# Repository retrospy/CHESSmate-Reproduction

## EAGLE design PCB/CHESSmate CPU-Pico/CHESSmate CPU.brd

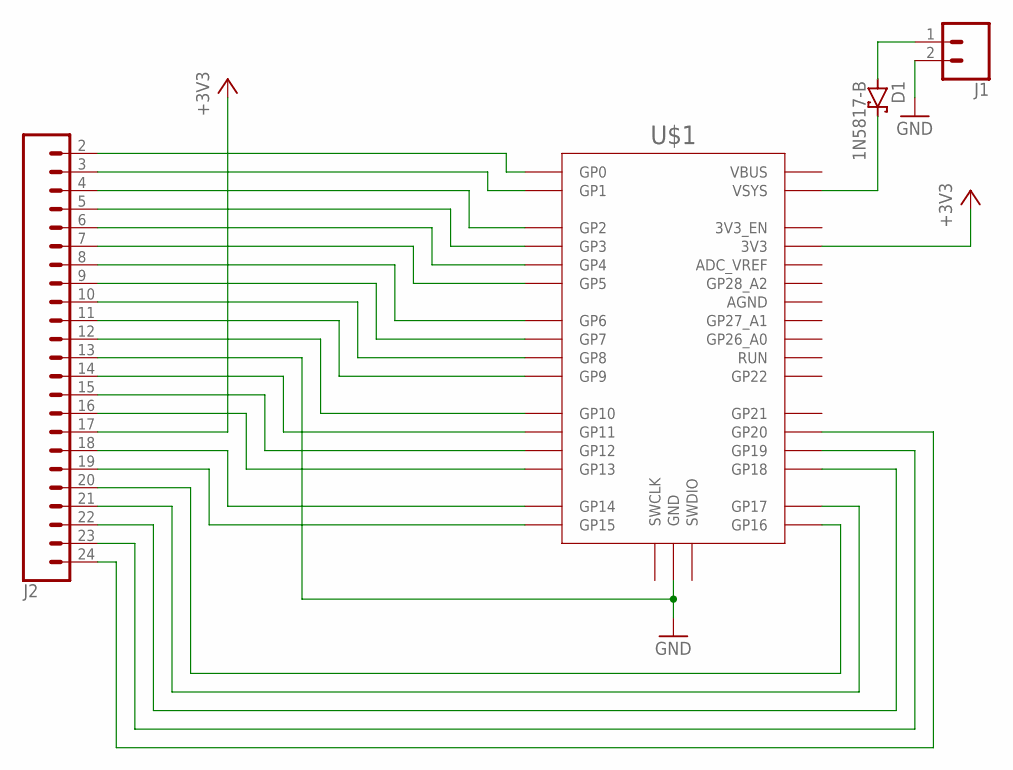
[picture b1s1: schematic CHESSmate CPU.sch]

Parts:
D1: 1N5817-B; DO41-7.6
J1: CONN_02; 1X02
J2: CONN_23; 1X23
U$1: RPI_PICO-TH; RPI_PICO_TH

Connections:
+3V3: J2.17, U$1.3V3
GND: J1.2, J2.13, U$1.GND@1 (GND), U$1.GND@2 (GND), U$1.GND@3 (GND), U$1.GND@4 (GND), U$1.GND@5 (GND), U$1.GND@6 (GND), U$1.GND@7 (GND), U$1.GND@8 (GND)
unnamed: D1.C, U$1.VSYS
unnamed: D1.A, J1.1
unnamed: J2.2, U$1.GP0
unnamed: J2.3, U$1.GP1
unnamed: J2.4, U$1.GP2
unnamed: J2.5, U$1.GP3
unnamed: J2.6, U$1.GP4
unnamed: J2.7, U$1.GP5
unnamed: J2.8, U$1.GP6
unnamed: J2.9, U$1.GP7
unnamed: J2.10, U$1.GP8
unnamed: J2.11, U$1.GP9
unnamed: J2.14, U$1.GP11
unnamed: J2.12, U$1.GP10
unnamed: J2.15, U$1.GP12
unnamed: J2.20, U$1.GP16
unnamed: J2.21, U$1.GP17
unnamed: J2.16, U$1.GP13
unnamed: J2.18, U$1.GP14
unnamed: J2.19, U$1.GP15
unnamed: J2.22, U$1.GP18
unnamed: J2.23, U$1.GP19
unnamed: J2.24, U$1.GP20

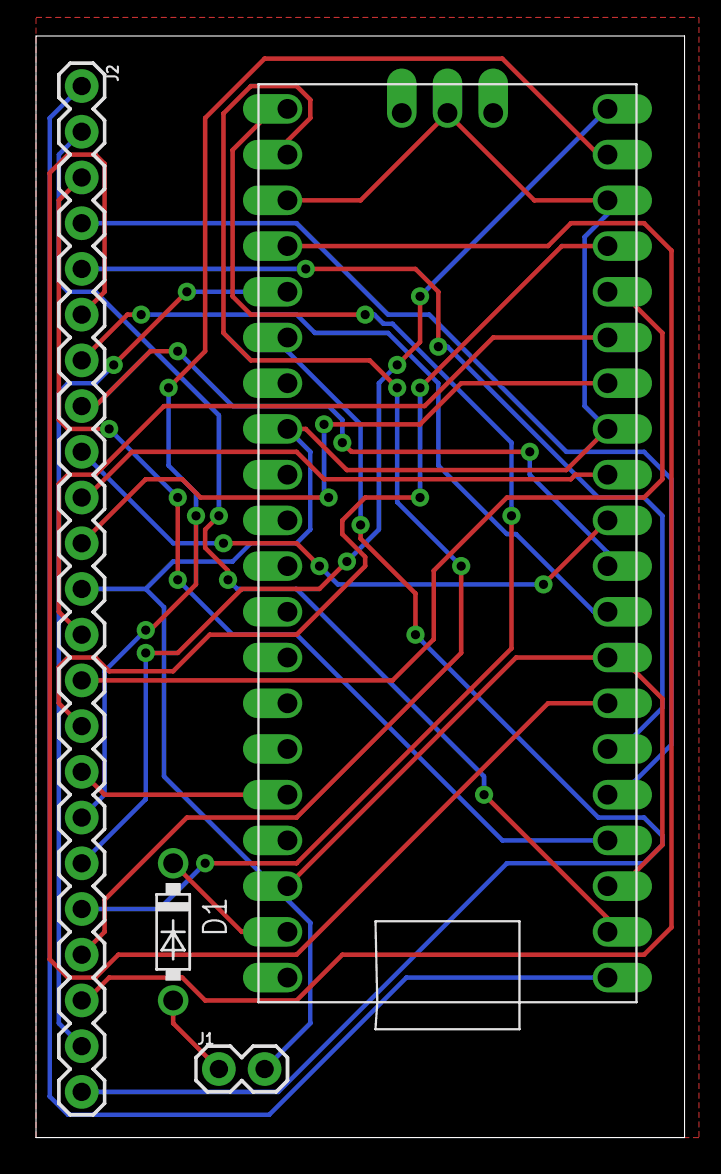
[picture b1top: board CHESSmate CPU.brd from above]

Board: 2 copper layers, 36.0 x 61.2 mm, 4 parts (0 on the bottom side), 25 nets.

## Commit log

2024-08-03 23 pin CPU connector
    This doesn't work because you can't use GPIO6, so I designed a new CPU board with a Pi Pico
2024-08-03 Updated Fabrication files
2024-08-03 Seperated the CPU into an ESP version and Pico Version
2024-08-03 Removing unneeded files
2024-08-10 Updated firmware

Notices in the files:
parts and their libraries:
SparkFun-Connectors: Licensing: Creative Commons ShareAlike 4.0 International - https://creativecommons.org/licenses/by-sa/4.0
